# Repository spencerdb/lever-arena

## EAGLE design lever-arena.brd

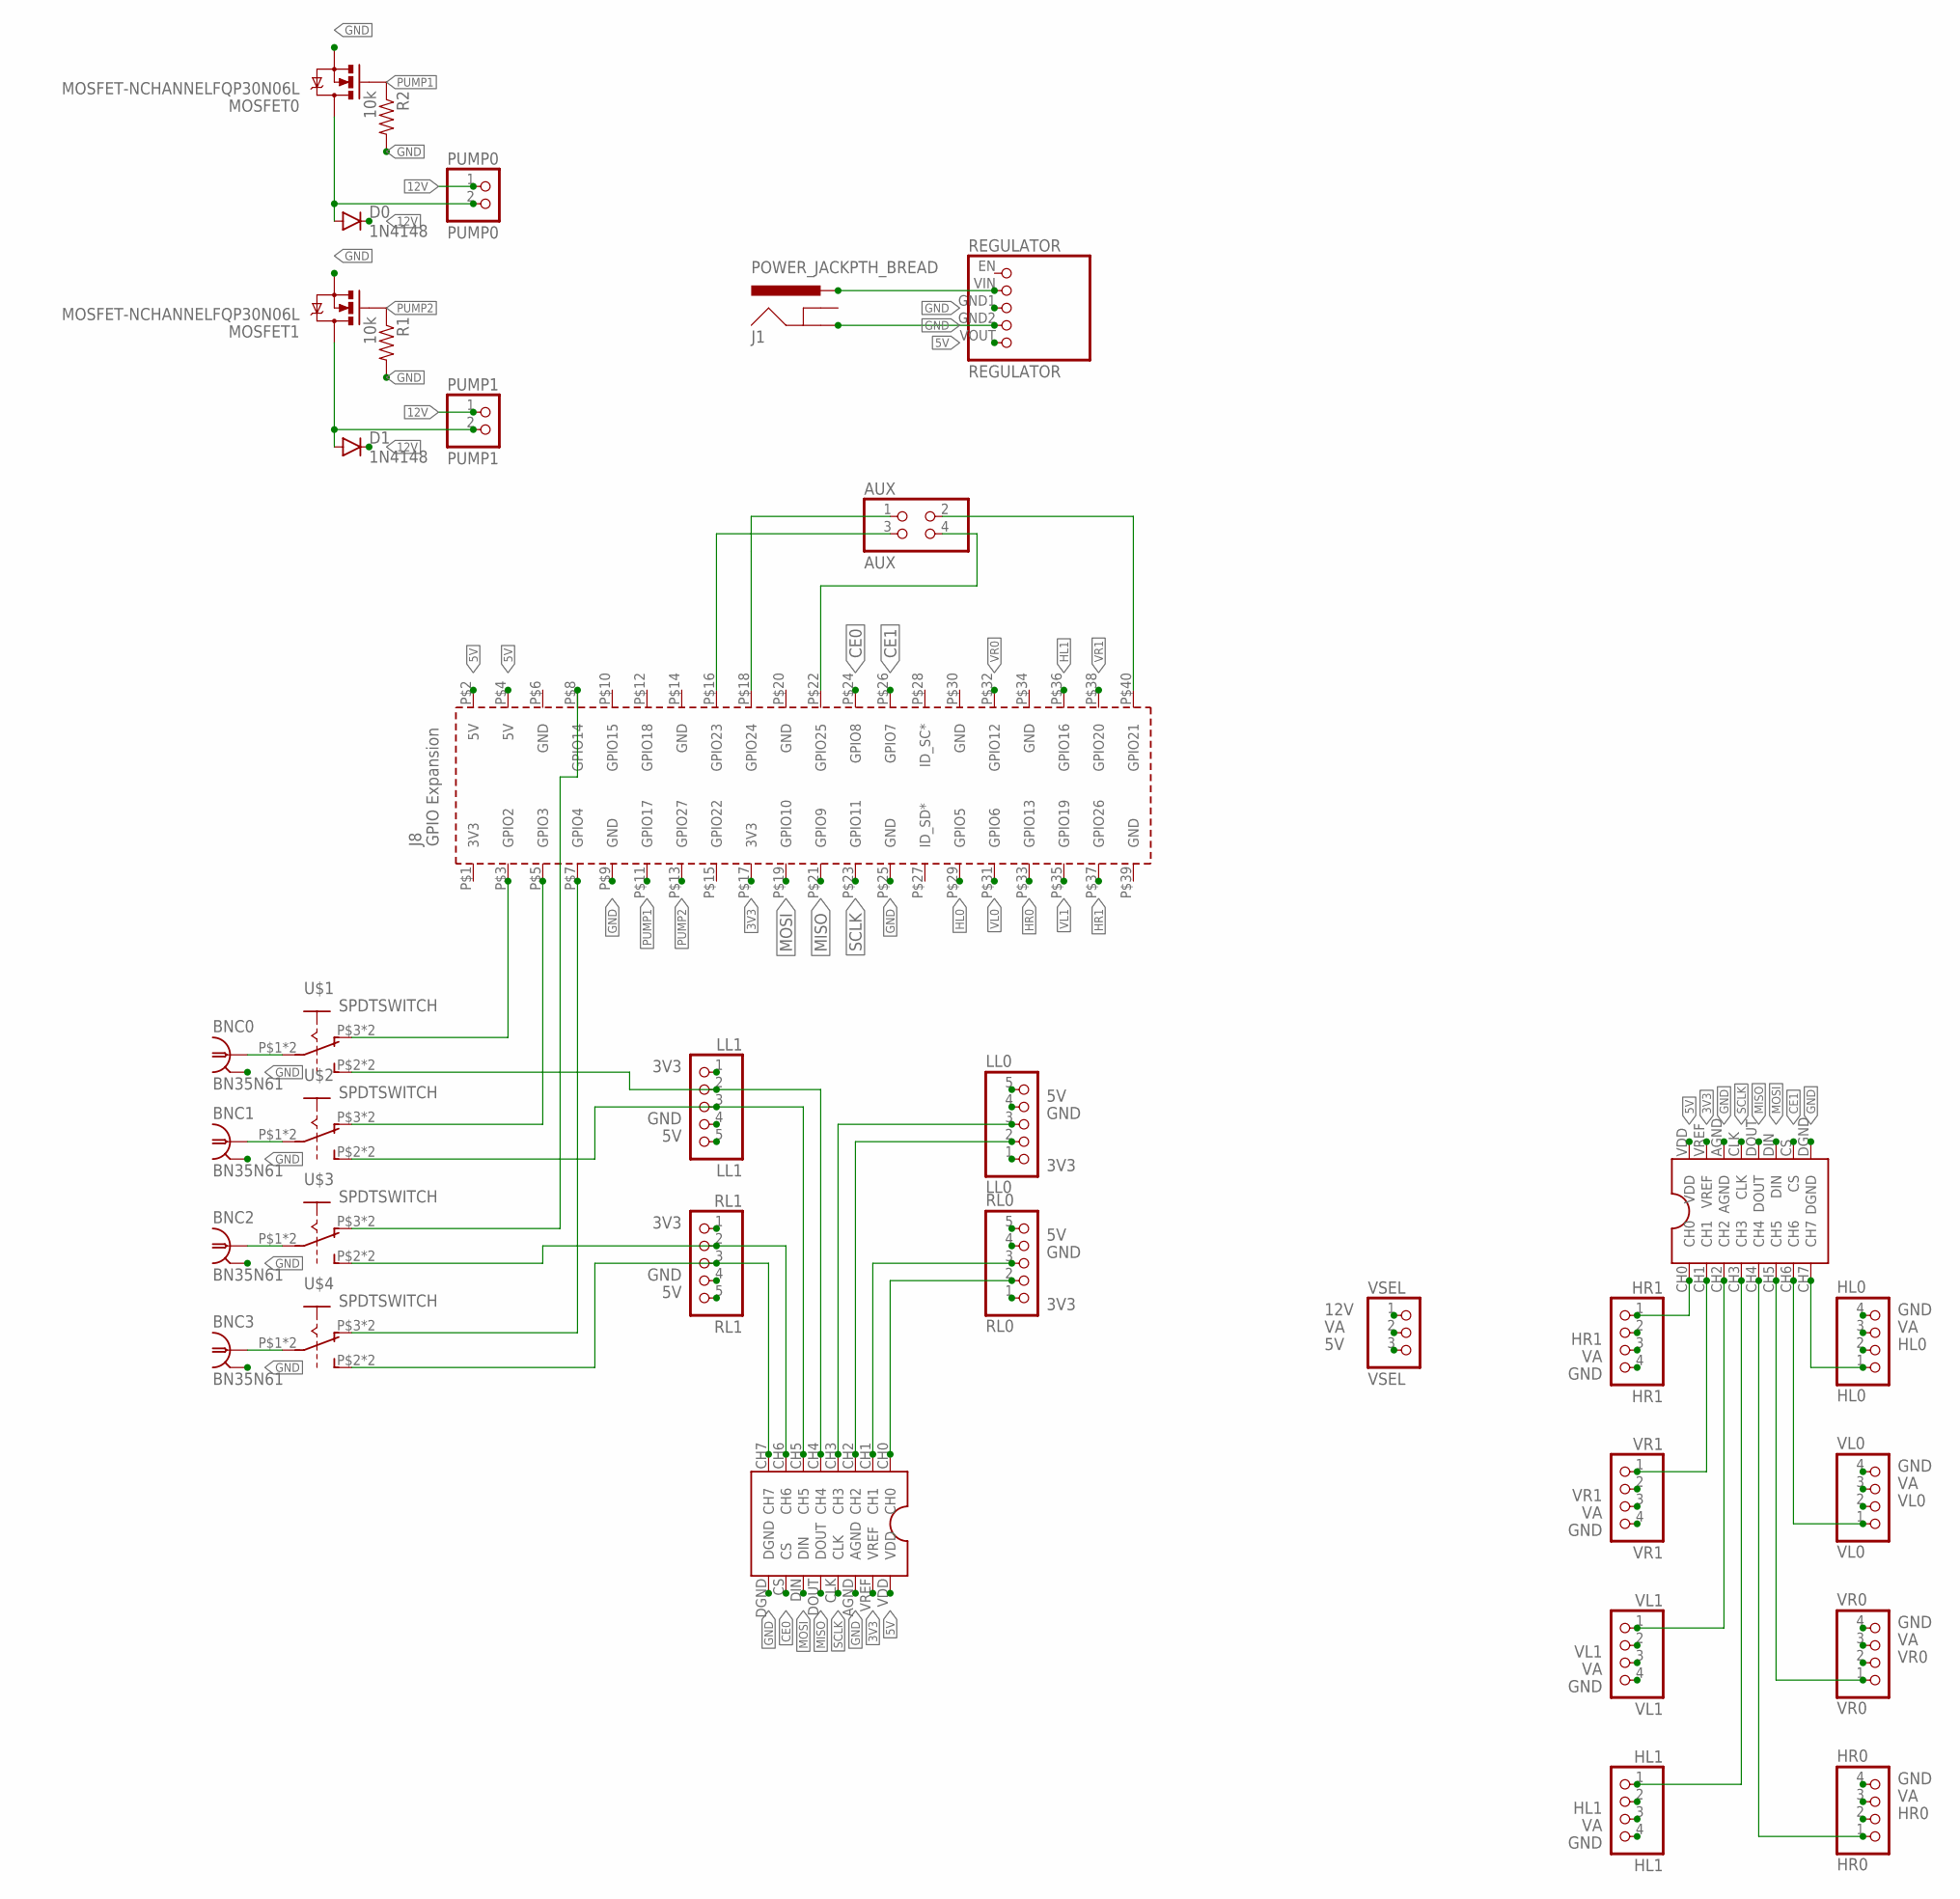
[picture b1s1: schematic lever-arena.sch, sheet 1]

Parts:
ADC0, ADC1: MCP3208; MCP3208-CI/SL
AUX: AUX; 2X02
BNC0, BNC1, BNC2, BNC3: BN35N61; B35N61
D0, D1: 1N4148; DIODE-1N4148
HL0: HL0; 1X04
HL1: HL1; 1X04
HR0: HR0; 1X04
HR1: HR1; 1X04
J1: POWER_JACKPTH_BREAD; POWER_JACK_PTH_BREAD
LL0: LL0; 1X05
LL1: LL1; 1X05
MOSFET0, MOSFET1: MOSFET-NCHANNELFQP30N06L; TO220V
PCB1: RPI3; RPI3H
PUMP0: PUMP0; 1X02
PUMP1: PUMP1; 1X02
R1, R2: 10k; AXIAL-0.3
REGULATOR: REGULATOR; POLOLU5V
RL0: RL0; 1X05
RL1: RL1; 1X05
U$1, U$2, U$3, U$4: SPDTSWITCH; JS202011CQNSPDT
VL0: VL0; 1X04
VL1: VL1; 1X04
VR0: VR0; 1X04
VR1: VR1; 1X04
VSEL: VSEL; 1X03

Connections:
3V3: ADC0.VREF, ADC1.VREF, LL0.1, LL1.1, PCB1.P$17 (3V3), RL0.1, RL1.1
5V: ADC0.VDD, ADC1.VDD, LL0.5, LL1.5, PCB1.P$2 (5V), PCB1.P$4 (5V), REGULATOR.VOUT, RL0.5, RL1.5, VSEL.3
12V: D0.C, D1.A, D1.C, J1.PWR, MOSFET1.2 (D), PUMP0.1, PUMP1.1, PUMP1.2, REGULATOR.VIN, VSEL.1
CE0: ADC0.CS, PCB1.P$24 (GPIO8)
CE1: ADC1.CS, PCB1.P$26 (GPIO7)
GND: ADC0.AGND, ADC0.DGND, ADC1.AGND, ADC1.DGND, BNC0.2, BNC0.3 (2), BNC0.4 (2), BNC0.5 (2), BNC1.2, BNC1.3 (2), BNC1.4 (2), BNC1.5 (2), BNC2.2, BNC2.3 (2), BNC2.4 (2), BNC2.5 (2), BNC3.2, BNC3.3 (2), BNC3.4 (2), BNC3.5 (2), HL0.4, HL1.4, HR0.4, HR1.4, J1.GND, LL0.4, LL1.4, MOSFET0.3 (S), MOSFET1.3 (S), PCB1.P$9 (GND), PCB1.P$25 (GND), R1.P$2 (2), R2.P$2 (2), REGULATOR.GND1, REGULATOR.GND2, RL0.4, RL1.4, VL0.4, VL1.4, VR0.4, VR1.4
HL0: HL0.2, PCB1.P$29 (GPIO5)
HL1: HL1.2, PCB1.P$36 (GPIO16)
HR0: HR0.2, PCB1.P$33 (GPIO13)
HR1: HR1.2, PCB1.P$37 (GPIO26)
MISO: ADC0.DOUT, ADC1.DOUT, PCB1.P$21 (GPIO9)
MOSI: ADC0.DIN, ADC1.DIN, PCB1.P$19 (GPIO10)
unnamed: PCB1.P$8 (GPIO14), U$3.P$3 (O), U$3.P$6 (O)
unnamed: ADC1.CH0, HR1.1
unnamed: D0.A, MOSFET0.2 (D), PUMP0.2
unnamed: PCB1.P$7 (GPIO4), U$4.P$3 (O), U$4.P$6 (O)
unnamed: BNC0.1, U$1.P$1, U$1.P$5
unnamed: PCB1.P$5 (GPIO3), U$2.P$3 (O), U$2.P$6 (O)
unnamed: PCB1.P$3 (GPIO2), U$1.P$3 (O), U$1.P$6 (O)
unnamed: BNC1.1, U$2.P$1, U$2.P$5
unnamed: BNC2.1, U$3.P$1, U$3.P$5
unnamed: BNC3.1, U$4.P$1, U$4.P$5
unnamed: ADC1.CH7, HL0.1
unnamed: ADC0.CH3, LL0.3
unnamed: ADC0.CH2, LL0.2
unnamed: ADC0.CH1, RL0.3
unnamed: ADC1.CH6, VL0.1
unnamed: ADC0.CH0, RL0.2
unnamed: AUX.3, PCB1.P$16 (GPIO23)
unnamed: AUX.1, PCB1.P$18 (GPIO24)
unnamed: ADC1.CH5, VR0.1
unnamed: AUX.4, PCB1.P$22 (GPIO25)
unnamed: AUX.2, PCB1.P$40 (GPIO21)
unnamed: ADC1.CH3, HL1.1
unnamed: ADC1.CH2, VL1.1
unnamed: ADC0.CH5, LL1.3, U$2.P$2 (S), U$2.P$4 (S)
unnamed: ADC0.CH4, LL1.2, U$1.P$2 (S), U$1.P$4 (S)
unnamed: ADC1.CH1, VR1.1
unnamed: ADC0.CH7, RL1.3, U$4.P$2 (S), U$4.P$4 (S)
unnamed: ADC0.CH6, RL1.2, U$3.P$2 (S), U$3.P$4 (S)
NGNG: ADC1.CH4, HR0.1
PUMP1: MOSFET0.1 (G), PCB1.P$11 (GPIO17), R2.P$1 (1)
PUMP2: MOSFET1.1 (G), PCB1.P$13 (GPIO27), R1.P$1 (1)
SCLK: ADC0.CLK, ADC1.CLK, PCB1.P$23 (GPIO11)
VA: HL0.3, HL1.3, HR0.3, HR1.3, VL0.3, VL1.3, VR0.3, VR1.3, VSEL.2
VL0: PCB1.P$31 (GPIO6), VL0.2
VL1: PCB1.P$35 (GPIO19), VL1.2
VR0: PCB1.P$32 (GPIO12), VR0.2
VR1: PCB1.P$38 (GPIO20), VR1.2

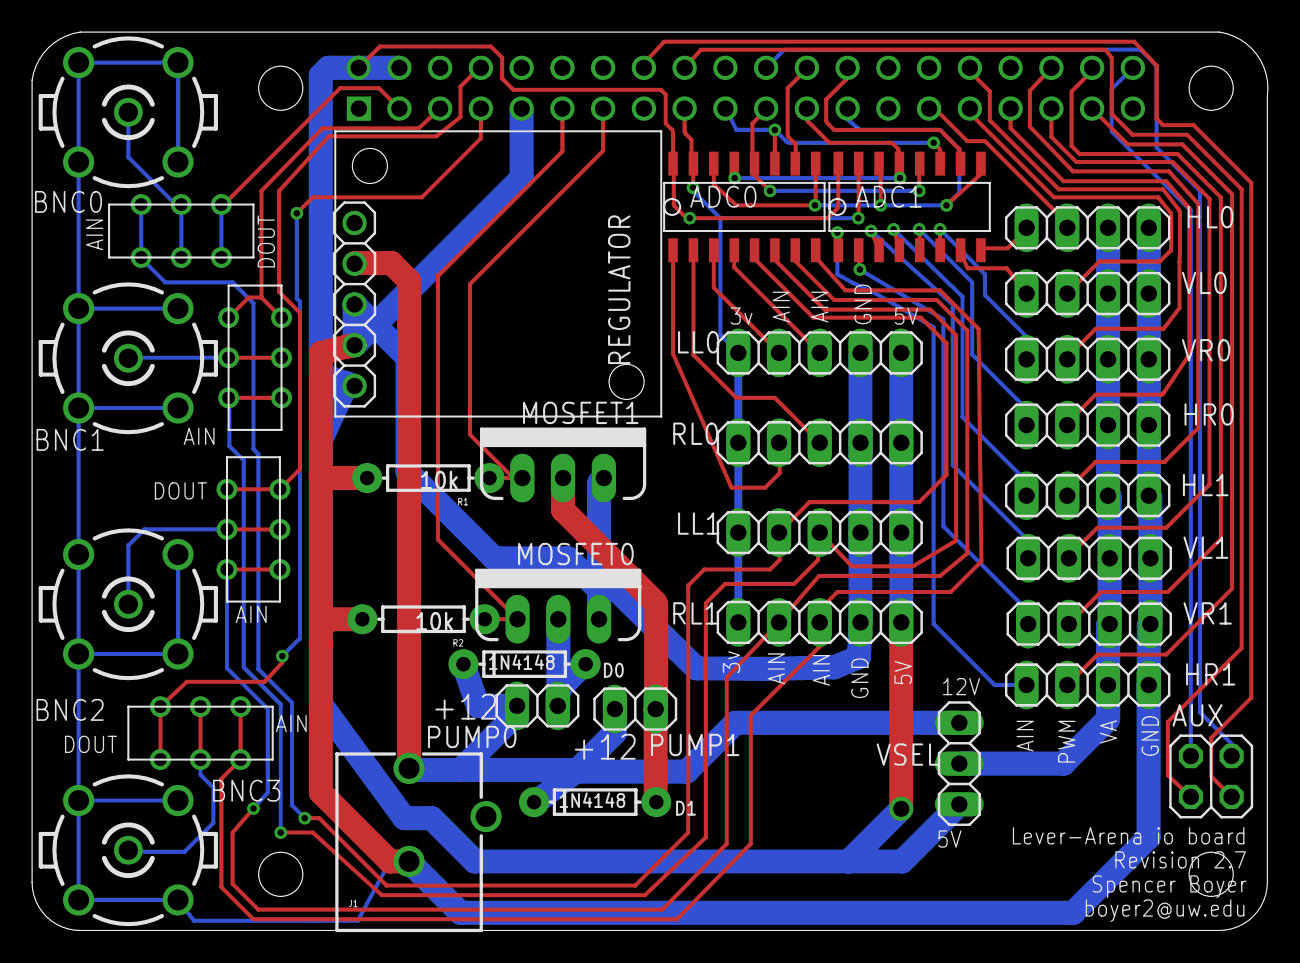
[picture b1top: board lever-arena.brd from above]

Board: 2 copper layers, 77.0 x 56.0 mm, 35 parts (0 on the bottom side), 49 nets.

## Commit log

2016-10-14 :tada: Added .gitattributes & .gitignore files
2016-10-17 added all components
2016-10-18 All connectors added
2016-10-18 REVISION 2.2
2016-10-18 added additional labels
2016-10-18 added labels
2016-10-18 Revision 2.3
2016-10-18 Revision 2.4
    routed connectors for adc input
2016-10-19 REVISION 2.5
2016-10-19 REVISION 2.6
    To be sent for fabrication
2016-10-19 REVISION 2.7
2016-10-26 updated materials list

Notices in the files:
parts and their libraries:
SparkFun-Connectors: Licensing: Creative Commons ShareAlike 4.0 International - https://creativecommons.org/licenses/by-sa/4.0
